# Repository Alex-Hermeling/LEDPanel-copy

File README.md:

# LEDPanel-copy

A KiCad project, version-controlled with the visual-diff half of the
[kicad-git-starter](https://github.com/Alex-Hermeling/kicad-git-starter) setup.

<!-- kicad-git-usage -->
## Using this repo

```bash
# save and close KiCad first, so the board is written and the .lck is gone
git switch -c feature/thing
git add -A
git commit -m "Add 3V3 regulator and decoupling"
git push -u origin HEAD
gh pr create --fill
```

The pull request gets an **interactive visual diff** of the schematic and the
layout, linked from a comment. Each open PR gets a page at
`https://Alex-Hermeling.github.io/LEDPanel-copy/pr-<number>/`, plus red/green PDFs as a
downloadable build artifact.

Tag revisions you actually send to fabrication — a tag is what makes "which
files did we build?" answerable a year later:

```bash
git tag -a rev-a -m "Sent to JLCPCB"
git push --tags
```

## Three habits specific to KiCad

**Close KiCad — or at least save — before committing.** KiCad holds edits in
memory and writes on save. Committing mid-edit captures a half-state that
doesn't match your screen.

**Commit the schematic and the layout together.** `.kicad_sch` and `.kicad_pcb`
share net and footprint identity. A schematic change without the matching layout
update is a broken state you can't cleanly return to.

**Don't expect merges to work on `.kicad_pcb`.** Because the files are text, git
*will* merge two divergent layouts and can produce a valid file with nonsense
geometry: overlapping footprints, traces to nowhere, silently dropped zones.
That's worse than a conflict, because nothing warns you. Branch freely for
schematic work, keep layout work linear, and redo a diverged layout rather than
merging it.

## What's tracked, and what isn't

Tracked: `*.kicad_pro`, `*.kicad_sch`, `*.kicad_pcb`, `*.kicad_dru`, and any
project-specific `*.kicad_sym` / `*.kicad_mod`.

Ignored: lock files, `*.kicad_prl` (per-user view settings), `*-backups/`,
autosaves, `fp-info-cache`, netlists and fabrication output. The rule of thumb:
**if KiCad can regenerate it, don't commit it.**

## Workflows

| Workflow | Trigger | Produces |
|---|---|---|
| `kicad-export.yml` | push to `main` | Schematic SVG/PDF and board PNGs, published to the `previews` branch |
| `kicad-diff.yml` | pull request | Interactive KiRi diff vs `main`, plus red/green PDFs |
| `kicad-pages.yml` | after a diff run | Publishes the diff sites to GitHub Pages |

This repo was set up with `--visual-diff-only`, so it has no "Repo file check"
workflow, no pre-commit hook and no branch protection. To add them later, run
`kicad-git-init.sh --no-create` here.

### Latest render of `main`

These appear after the first run of the export workflow.

**Schematic** ([PDF](https://github.com/Alex-Hermeling/LEDPanel-copy/raw/previews/schematic/schematic.pdf))

**PCB**

| Top | Bottom |
|---|---|
|  |  |

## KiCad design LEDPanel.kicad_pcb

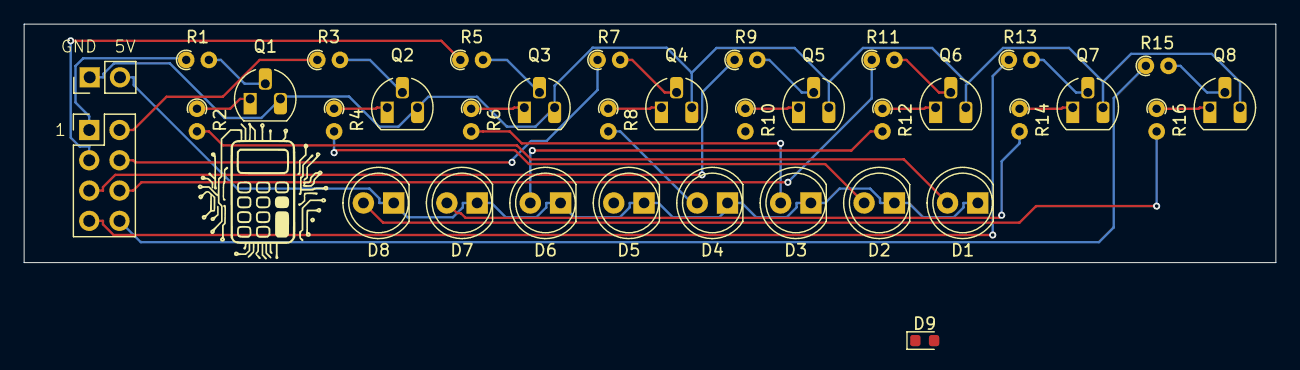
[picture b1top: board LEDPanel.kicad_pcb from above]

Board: 2 copper layers, 105.0 x 20.0 mm, 35 parts (0 on the bottom side), 34 nets.

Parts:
D1, D2, D3, D4, D5, D6, D7, D8: LED; LED_D5.0mm
D9: LED; LED_0603_1608Metric
J1: Conn_01x08_Pin; PinHeader_2x04_P2.54mm_Vertical
J2: Conn_01x02_Pin; PinHeader_1x02_P2.54mm_Vertical
Q1, Q2, Q3, Q4, Q5, Q6, Q7, Q8: 2N3904; TO-92_HandSolder
R1, R3, R5, R7, R9, R11, R13, R15: 220k; R_Axial_DIN0204_L3.6mm_D1.6mm_P1.90mm_Vertical
R2, R4, R6, R8, R10, R12, R14, R16: 330; R_Axial_DIN0204_L3.6mm_D1.6mm_P1.90mm_Vertical

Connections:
unnamed: D1.2 (A), R2.2
unnamed: D1.1 (K), D2.1 (K), D3.1 (K), D4.1 (K), D5.1 (K), D6.1 (K), D7.1 (K), D8.1 (K), J2.2
unnamed: D2.2 (A), R4.2
unnamed: D3.2 (A), R6.2
unnamed: D4.2 (A), R8.2
unnamed: D5.2 (A), R10.2
unnamed: D6.2 (A), R12.2
unnamed: D7.2 (A), R14.2
unnamed: D8.2 (A), R16.2
unnamed: J1.1, R1.1
unnamed: J1.2, R3.1
unnamed: J1.3, R5.1
unnamed: J1.4, R7.1
unnamed: J1.5, R9.1
unnamed: J1.6, R11.1
unnamed: J1.7, R13.1
unnamed: J1.8, R15.1
unnamed: Q1.2 (B), R1.2
unnamed: Q1.1 (E), R2.1
unnamed: Q2.2 (B), R3.2
unnamed: Q2.1 (E), R4.1
unnamed: Q3.2 (B), R5.2
unnamed: Q3.1 (E), R6.1
unnamed: Q4.2 (B), R7.2
unnamed: Q4.1 (E), R8.1
unnamed: Q5.2 (B), R9.2
unnamed: Q5.1 (E), R10.1
unnamed: Q6.2 (B), R11.2
unnamed: Q6.1 (E), R12.1
unnamed: Q7.2 (B), R13.2
unnamed: Q7.1 (E), R14.1
unnamed: Q8.2 (B), R15.2
unnamed: Q8.1 (E), R16.1
test4: D9.1 (K), J2.1, Q1.3 (C), Q2.3 (C), Q3.3 (C), Q4.3 (C), Q5.3 (C), Q6.3 (C), Q7.3 (C), Q8.3 (C)
